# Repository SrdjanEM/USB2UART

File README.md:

# USB2UART Programmer

This project provides a simple USB to UART programmer that integrates useful features for programming microcontrollers. It is based on the FTDI FT230 chip and features USB Type-C connectivity, BOOT and EN/RESET buttons, as well as multiple connector options including a UART header and a TC2030 connector.

---

## Features

1. **USB Type-C Connector**
   - Modern and versatile USB interface for power and data transfer.

2. **FTDI FT230 Chip**
   - Reliable USB to UART communication.
   - Supports various baud rates and low-latency operation.

3. **BOOT and EN/RESET Buttons**
   - Simplifies the programming process by providing dedicated buttons:
     - **BOOT**: Configures the microcontroller for firmware upload.
     - **EN/RESET**: Resets the microcontroller or triggers a reinitialization.

4. **UART Header**
   - Standard 4-pin UART header for easy interfacing with target devices.

5. **TC2030 Connector**
   - Additional programming interface for Tag-Connect cable compatibility.

---

## Applications

- Programming microcontrollers such as ESP32, STM32, and similar.
- Debugging embedded systems.
- Prototyping and testing UART-based devices.

---

## Hardware Components

1. **FTDI FT230 Chip**
   - Manages USB to UART communication.
2. **USB Type-C Connector**
   - Ensures robust and reversible connections.
3. **Push Buttons**
   - **BOOT**: Activates bootloader mode.
   - **EN/RESET**: Triggers a reset of the target device.
4. **Connectors**
   - **UART Header**: Pinout: VCC, TXD, RXD, GND.
   - **TC2030 Connector**: 6-pin layout compatible with Tag-Connect cables.

---

## Pinout

### UART Header:
| Pin | Signal  |
|-----|---------|
| 1   | VCC     |
| 2   | RXD     |
| 3   | TXD     |
| 4   | GND     |

### TC2030 Connector:
| Pin | Signal  |
|-----|---------|
| 1   | VCC     |
| 2   | GND     |
| 3   | EN      |
| 4   | BOOT     |
| 5   | TXD    |
| 6   | RXD    |

---

## Schematic Overview

---

## Usage Instructions

1. **Connect the Programmer**
   - Plug the USB Type-C cable into your computer and the programmer.
   - Connect the UART header or TC2030 connector to your target device.

2. **Install Drivers**
   - Ensure FTDI drivers are installed on your computer. These can be downloaded from the [FTDI website](https://www.ftdichip.com/).

3. **Programming**
   - Press the BOOT button while resetting the device with the EN/RESET button to enter bootloader mode.
   - Use your preferred programming tool (e.g., esptool.py, STM32CubeProgrammer).

4. **Debugging**
   - Monitor UART communication using any serial terminal application.

---

## Additional Notes

- Ensure the target device’s UART voltage levels are compatible with the FT230’s logic level (typically 3.3V).
- The TC2030 connector is designed for Tag-Connect cables, making it ideal for quick and reliable programming connections without the need for soldering headers.
- Use quality USB Type-C cables to ensure stable power and data transmission.
- **USB2UART device also has a 3.3V voltage regulator to allow for powering of devices if they are not 5V compatible.**

---

## License

This project is open-source under the [GNU Public License](LICENSE). Feel free to modify and use it in your projects.

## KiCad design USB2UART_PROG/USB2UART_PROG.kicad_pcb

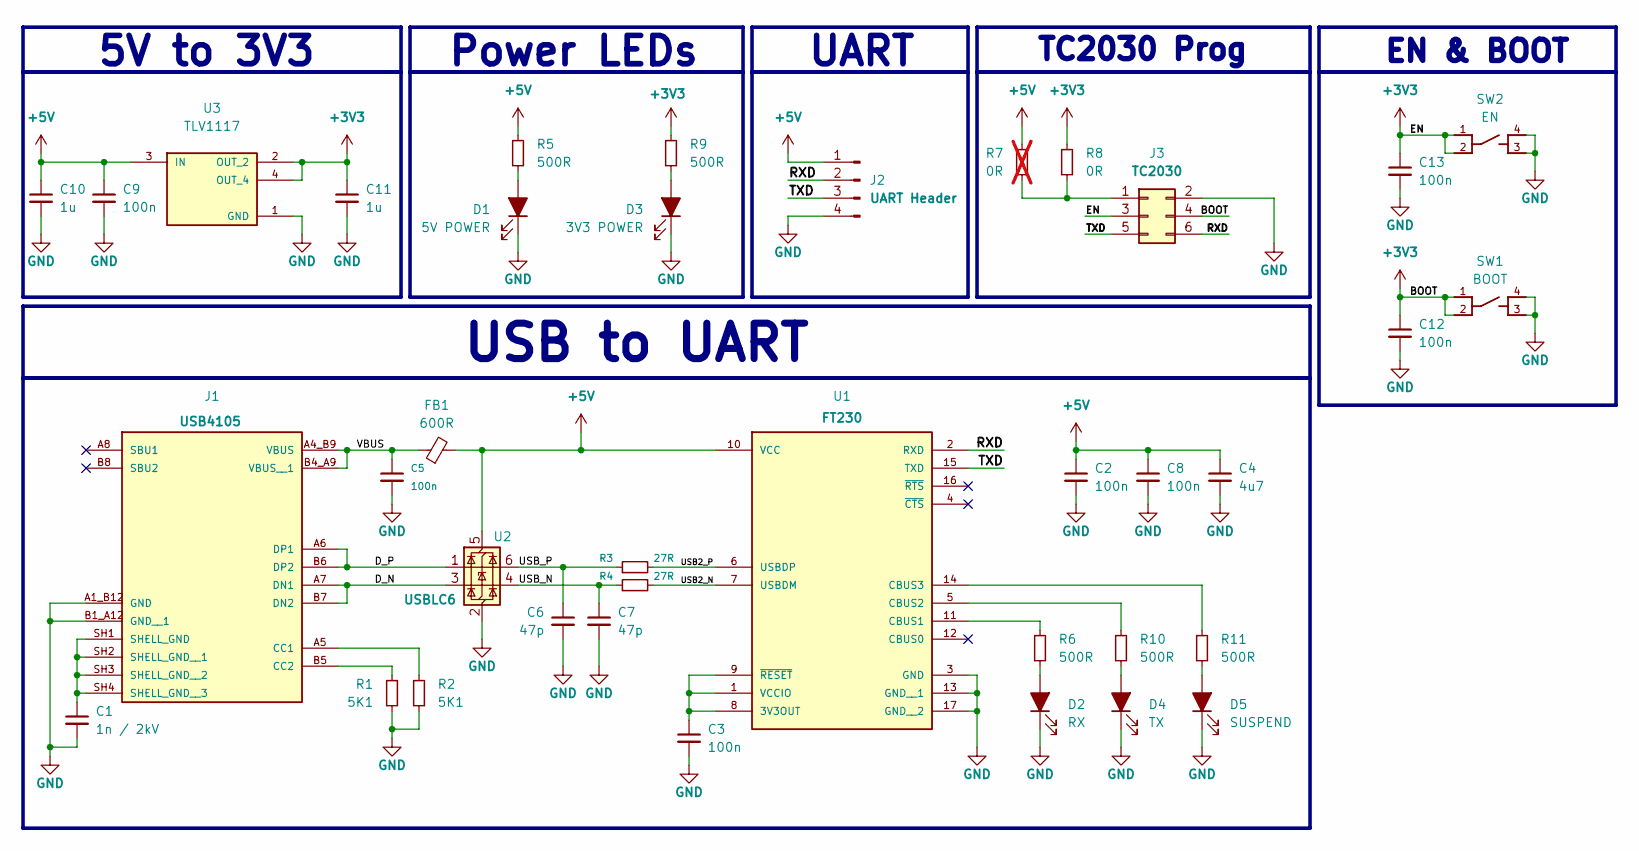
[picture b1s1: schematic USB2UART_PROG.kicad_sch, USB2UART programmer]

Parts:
C1: 1n / 2kV; C_1206_3216Metric; MPN C1206C102KGRACTU; Digikey stock 614,131 - 24/12/2024
C2, C3, C5, C8, C9, C12, C13: 100n; C_0603_1608Metric; MPN CC0603KRX7R7BB104; Digikey stock 8,314,003 - 23/12/2024
C4: 4u7; C_0603_1608Metric; MPN CL10A475KP8NNNC; Digikey stock 6,283,855 - 23/12/2024
C6: 47p; C_0603_1608Metric; MPN CL10C470JB8NNNC; Digikey stock 8,314,003 - 23/12/2024
C7: 47p; C_0603_1608Metric; MPN CL10C470JB8NNNC; Digikey stock 1,979,713 - 23/12/2024
C10, C11: 1u; C_0603_1608Metric; MPN CC0603KRX7R7BB105; Digikey stock 8,975,196 - 24/12/2024
D1: 5V POWER; LED_0603_1608Metric; MPN 150060GS75000; Digikey stock 129,006 - 23/12/2024
D2: RX; LED_0603_1608Metric; MPN 150060YS75000; Digikey stock 15,103 - 23/12/2024
D3: 3V3 POWER; LED_0603_1608Metric; MPN 150060GS75000; Digikey stock 129,006 - 23/12/2024
D4: TX; LED_0603_1608Metric; MPN 150060YS75000; Digikey stock 15,103 - 23/12/2024
D5: SUSPEND; LED_0603_1608Metric; MPN 150060YS75000; Digikey stock 15,103 - 23/12/2024
FB1: 600R; L_0805_2012Metric; MPN MI0805K601R-10; Digikey stock 319,953 - 23/12/2024
J1: USB4105; MPN USB4105-GF-A; Digikey stock 69,965 - 23/12/2024
J2: UART Header; PinHeader_1x04_P2.54mm_Vertical; MPN 61300411121; Digikey stock 33,682 - 23/12/2024
J3: TC2030; PinHeader_2x03_P2.54mm_Vertical; MPN PH2-06-UA; Digikey stock 7,660 - 24/12/2024
R1, R2: 5K1; R_0603_1608Metric; MPN RC0603FR-075K1L; Digikey stock 1,826,291 - 23/12/2024
R3, R4: 27R; R_0603_1608Metric; MPN RC0603FR-0727RL; Digikey stock 289,460 - 23/12/2024
R5, R6, R9, R10, R11: 500R; R_0603_1608Metric; MPN RT0603BRC07500RL; Digikey stock 24,256 - 23/12/2024
R7: 0R; R_0603_1608Metric; MPN RMCF0603ZT0R00; Digikey stock 4,580,806 - 24/12/2024; not fitted
R8: 0R; R_0603_1608Metric; MPN RMCF0603ZT0R00; Digikey stock 4,580,806 - 24/12/2024
SW1: BOOT; SW_PTS810_SJM_250_SMTR_LFS; MPN PTS815SJM250SMTRLFS; Digikey stock 15,811 - 23/12/2024
SW2: EN; SW_PTS810_SJM_250_SMTR_LFS; MPN PTS815SJM250SMTRLFS; Digikey stock 15,811 - 23/12/2024
U1: FT230; FT230XQ-QFN65P; MPN FT230XQ-R; Digikey stock 39,907 - 23/12/2024
U2: USBLC6; SOT-666; MPN USBLC6-2P6; Digikey stock 48,927 -23/12/2024
U3: TLV1117; VREG_TLV1117LV33DCYR; MPN TLV1117LV33DCYR; Digikey stock 18,033 - 24/12/2024

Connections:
+3V3: C11.1, C12.1, C13.1, J3.3, J3.4, R8.1, R9.1, SW1.1, SW1.2, SW2.1, SW2.2, U3.2 (OUT_2), U3.4 (OUT_4)
+5V: C2.1, C4.1, C8.1, C9.1, C10.1, FB1.2, J2.1, R5.1, R7.1, U1.10 (VCC), U2.5 (VBUS), U3.3 (IN)
/D_N: J1.A7 (DN1), J1.B7 (DN2), U2.3 (I/O2)
/D_P: J1.A6 (DP1), J1.B6 (DP2), U2.1 (I/O1)
/RXD: J2.2, J3.6, U1.2 (RXD)
/TXD: J2.3, J3.5, U1.15 (TXD)
/USB2_N: R4.2, U1.7 (USBDM)
/USB2_P: R3.2, U1.6 (USBDP)
/USB_N: C7.1, R4.1, U2.4 (I/O2)
/USB_P: C6.1, R3.1, U2.6 (I/O1)
/VBUS: C5.1, FB1.1, J1.A4_B9 (VBUS), J1.B4_A9 (VBUS__1)
GND: C1.2, C2.2, C3.2, C4.2, C5.2, C6.2, C7.2, C8.2, C9.2, C10.2, C11.2, C12.2, C13.2, D1.1 (K), D2.1 (K), D3.1 (K), D4.1 (K), D5.1 (K), J1.A1_B12 (GND), J1.B1_A12 (GND__1), J2.4, J3.2, R1.2, R2.2, SW1.3, SW1.4, SW2.3, SW2.4, U1.3 (GND), U1.13 (GND__1), U1.17 (GND__2), U2.2 (GND), U3.1 (GND)
unnamed: D1.2 (A), R5.2
unnamed: D2.2 (A), R6.2
unnamed: D3.2 (A), R9.2
unnamed: D4.2 (A), R10.2
unnamed: D5.2 (A), R11.2
unnamed: J1.A5 (CC1), R2.1
unnamed: J1.B5 (CC2), R1.1
unnamed: C1.1, J1.SH1 (SHELL_GND), J1.SH2 (SHELL_GND__1), J1.SH3 (SHELL_GND__2), J1.SH4 (SHELL_GND__3)
unnamed: J3.1, R7.2, R8.2
unnamed: C3.1, U1.1 (VCCIO), U1.8 (3V3OUT), U1.9 (~RESET)
unnamed: R6.1, U1.11 (CBUS1)
unnamed: R10.1, U1.5 (CBUS2)
unnamed: R11.1, U1.14 (CBUS3)

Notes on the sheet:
5V to 3V3
TC2030 Prog
UART
Power LEDs
USB to UART
EN & BOOT

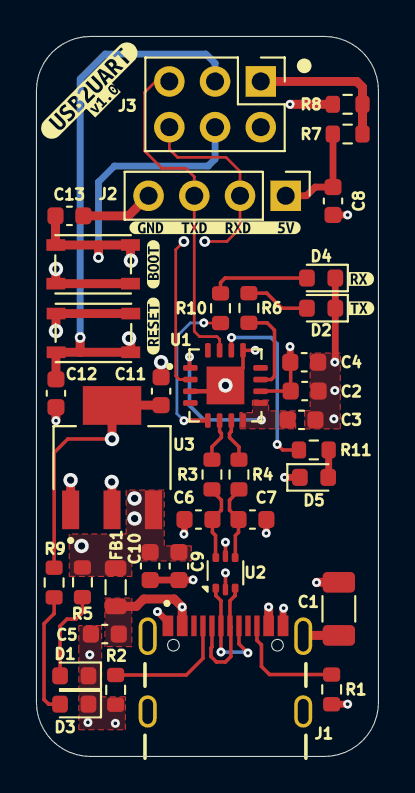
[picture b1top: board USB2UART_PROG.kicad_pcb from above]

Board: 4 copper layers, 19.0 x 40.0 mm, 45 parts (0 on the bottom side), 25 nets.

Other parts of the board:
kibuzzard-676AD2A0: G***; kibuzzard-676AD2A0
kibuzzard-676AD2BA: G***; kibuzzard-676AD2BA
kibuzzard-676AD3C3: G***; kibuzzard-676AD3C3
kibuzzard-676AD42F: G***; kibuzzard-676AD42F
kibuzzard-676AD395: G***; kibuzzard-676AD395
kibuzzard-676ADB76: G***; kibuzzard-676ADB76
kibuzzard-676ADB82: G***; kibuzzard-676ADB82

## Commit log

2024-12-24 Added Hardware files
    Add Hardware file that have been created using KiCad 8.0.7
2024-12-24 BOOT & RESET ISSUE
    Fixed a wrong connection with B&R buttons.
